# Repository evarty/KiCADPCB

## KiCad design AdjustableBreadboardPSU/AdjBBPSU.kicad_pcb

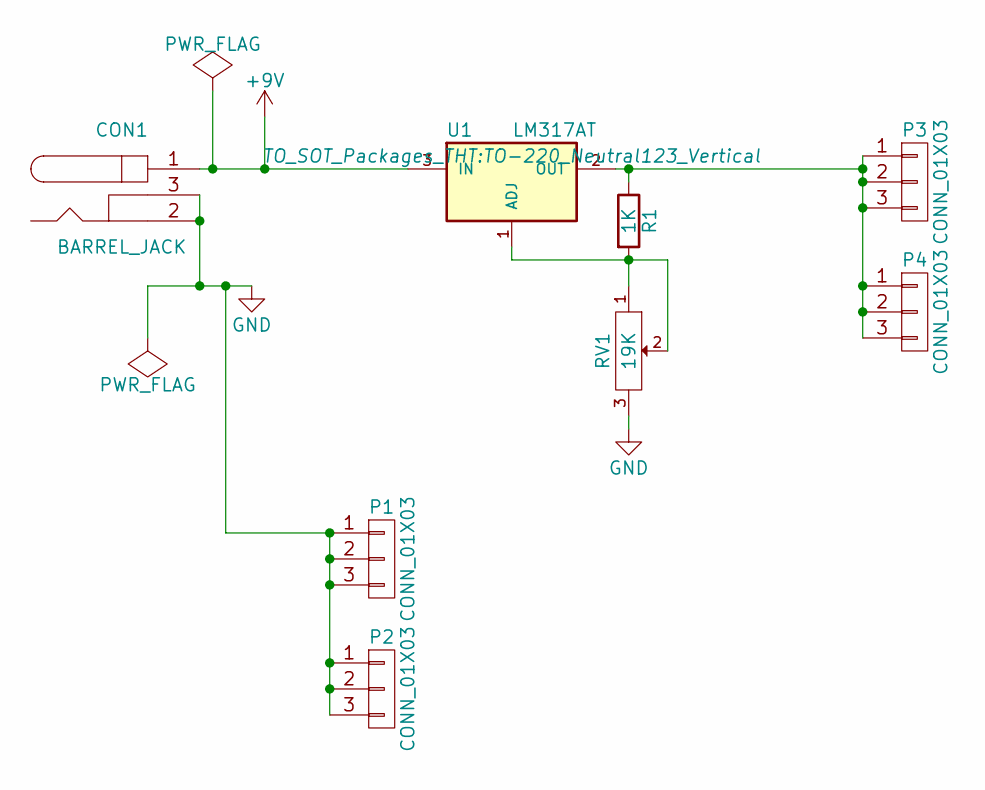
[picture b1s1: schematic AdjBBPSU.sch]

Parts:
CON1: BARREL_JACK
P1, P2, P3, P4: CONN_01X03; Pin_Header_Straight_1x03
R1: 1K; Resistor_Horizontal_RM20mm
RV1: 19K; SalvagedPotFootprint
U1: LM317AT; TO-220_Neutral123_Vertical

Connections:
+9V: CON1.1, U1.3 (IN)
GND: CON1.2, CON1.3, P1.1, P1.2, P1.3, P2.1, P2.2, P2.3, RV1.3
unnamed: P3.1, P3.2, P3.3, P4.1, P4.2, P4.3, R1.1, U1.2 (OUT)
unnamed: R1.2, RV1.1, RV1.2, U1.1 (ADJ)

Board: 2 copper layers, 8 parts (0 on the bottom side), 4 nets, no tracks yet.

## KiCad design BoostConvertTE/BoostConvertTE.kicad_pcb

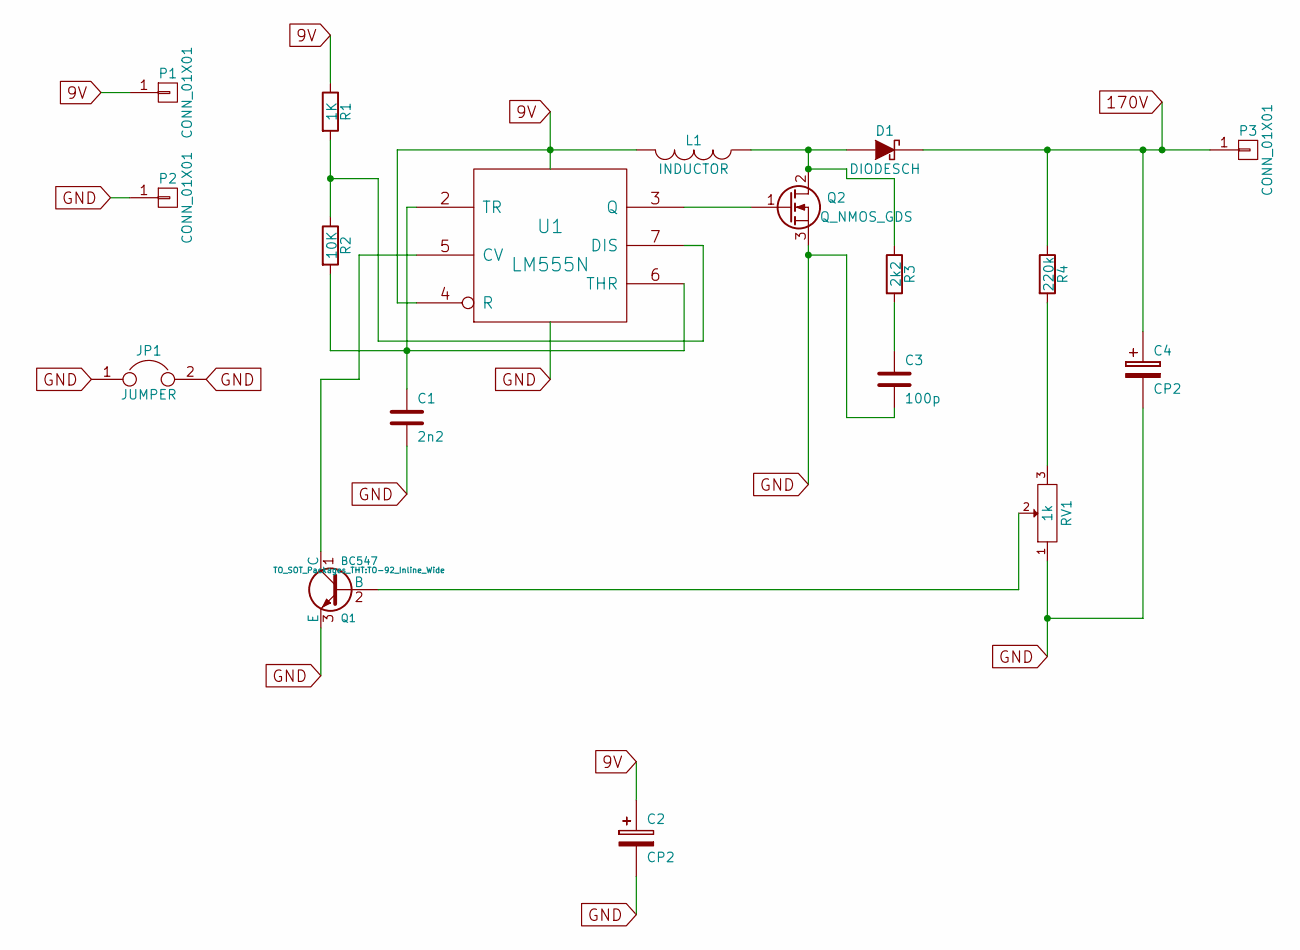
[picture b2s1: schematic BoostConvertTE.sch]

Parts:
C1: 2n2; C_Rect_L7_W2.5_P5
C2: CP2; C_Radial_D10_L13_P5
C3: 100p; C_Rect_L7_W2.5_P5
C4: CP2; C_Rect_L27_W9_H17_P23
D1: DIODESCH; D3
JP1: JUMPER; R3
L1: INDUCTOR; C_Radial_D10_L13_P5
P1, P2, P3: CONN_01X01; Pin_Header_Straight_1x01
Q1: BC547; TO-92_Inline_Wide
Q2: Q_NMOS_GDS; TO-220_Neutral123_Vertical
R1: 1K; Resistor_Horizontal_RM10mm
R2: 10K; Resistor_Horizontal_RM10mm
R3: 2k2; Resistor_Horizontal_RM10mm
R4: 220k; Resistor_Horizontal_RM10mm
RV1: 1k; TO-220_Neutral123_Horizontal
U1: LM555N; DIP-8_W7.62mm_LongPads

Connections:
9V: C2.1, L1.2, P1.1, R1.1, U1.4 (R), U1.8 (VCC)
170V: C4.1, D1.2 (K), P3.1, R4.1
GND: C1.2, C2.2, C3.2, C4.2, JP1.1, JP1.2, P2.1, Q1.3 (E), Q2.3 (S), RV1.1, U1.1 (GND); also elsewhere on the board
unnamed: C1.1, R2.2, U1.2 (TR), U1.6 (THR)
unnamed: C3.1, R3.2
unnamed: D1.1 (A), L1.1, Q2.2 (D), R3.1
unnamed: Q1.1 (C), U1.5 (CV)
unnamed: Q1.2 (B), RV1.2
unnamed: Q2.1 (G), U1.3 (Q)
unnamed: R1.2, R2.1, U1.7 (DIS)
unnamed: R4.2, RV1.3

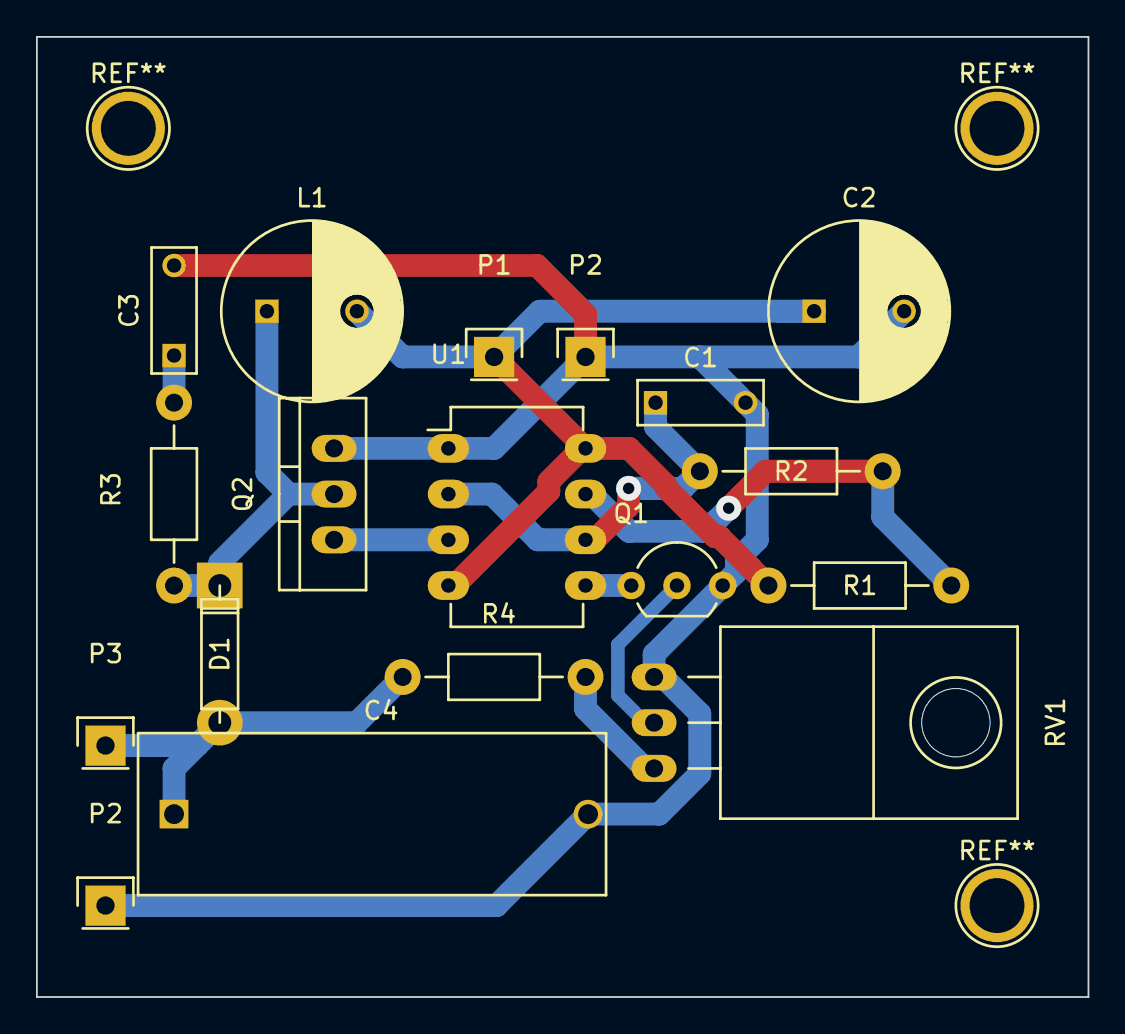
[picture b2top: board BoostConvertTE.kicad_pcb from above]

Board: 2 copper layers, 58.4 x 53.3 mm, 18 parts (0 on the bottom side), 11 nets.

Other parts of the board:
P2#2: CONN_01X01; Pin_Header_Straight_1x01

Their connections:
GND: P2#2.1; also elsewhere on the board

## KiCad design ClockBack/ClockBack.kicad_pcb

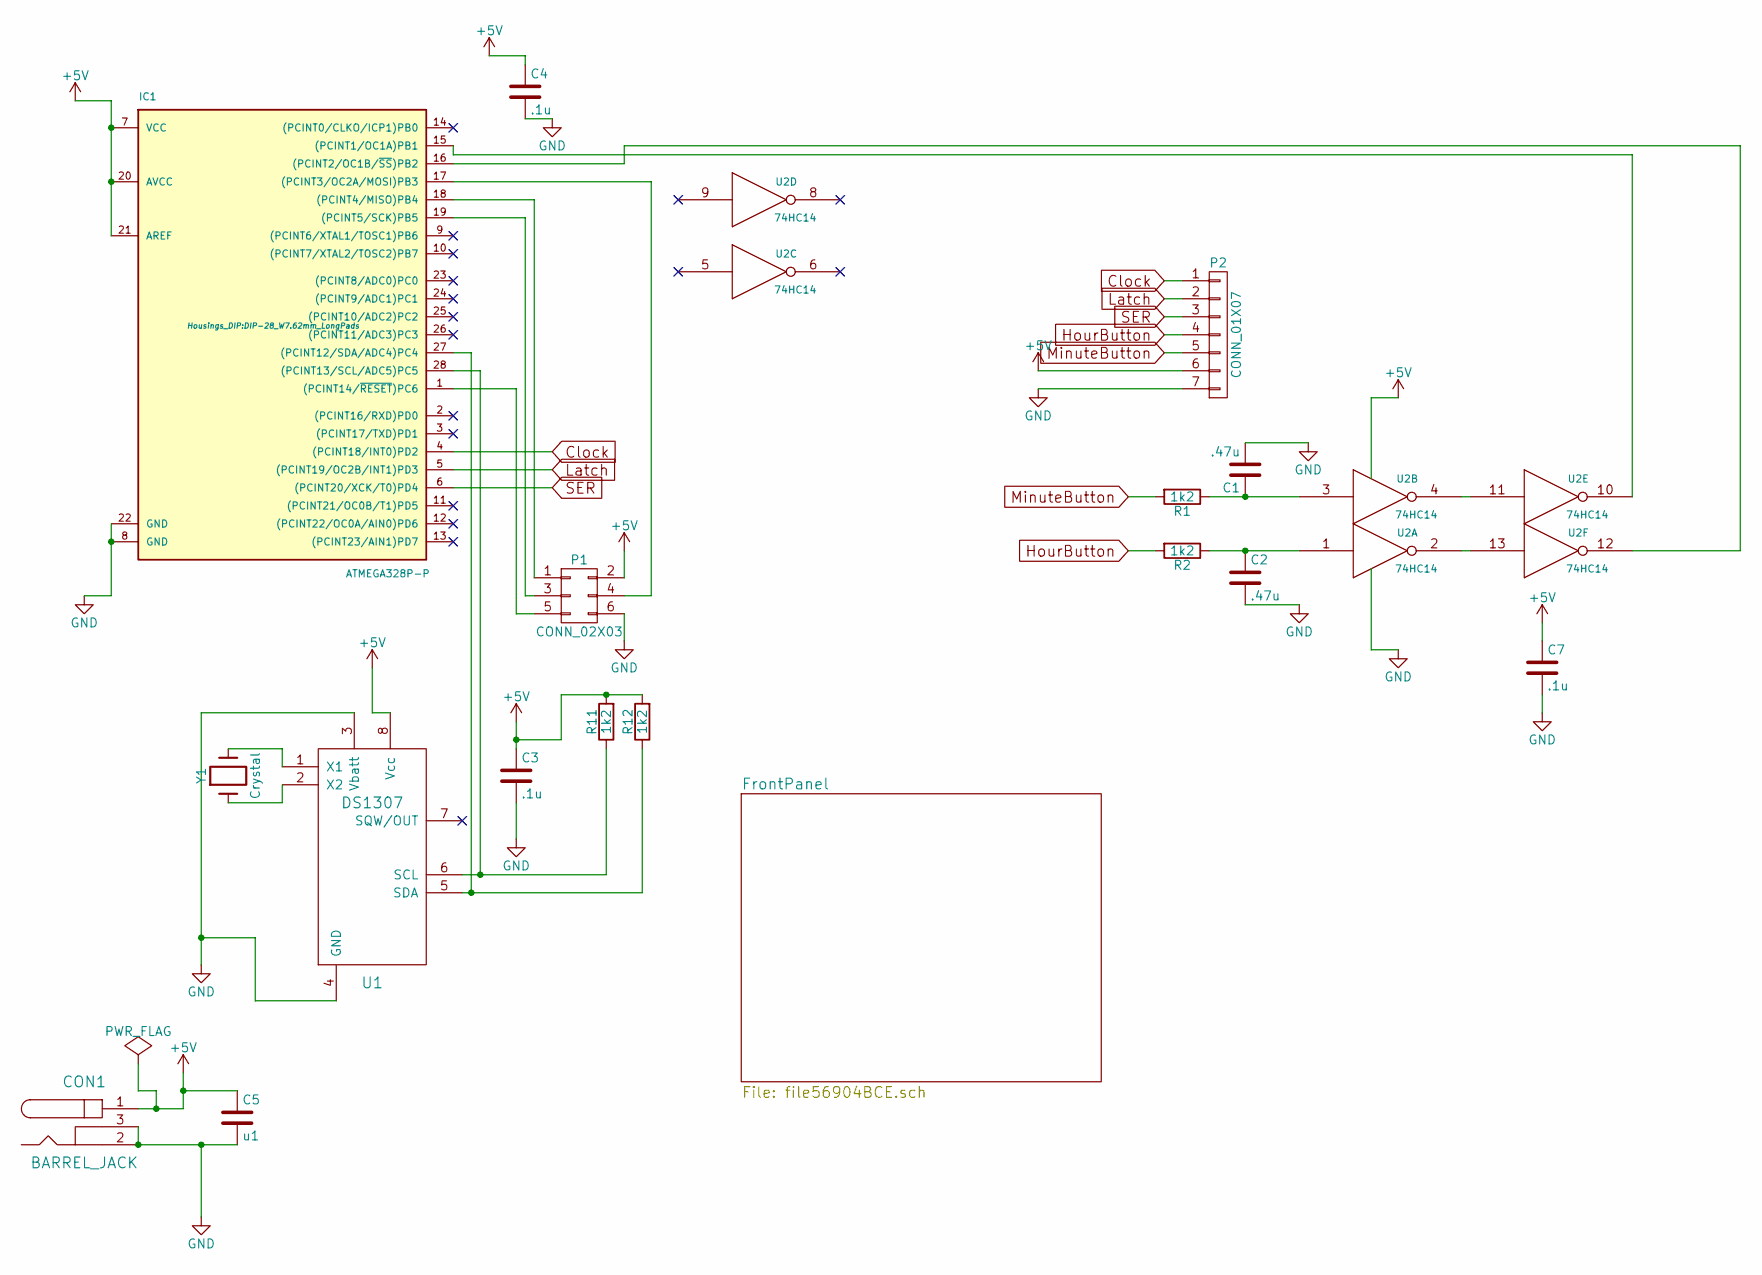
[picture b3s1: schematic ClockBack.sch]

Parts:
C1, C2: .47u; C_Disc_D6_P5
C3, C4, C7: .1u; C_Disc_D6_P5
C5: u1; C_Disc_D6_P5
CON1: BARREL_JACK
IC1: ATMEGA328P-P; DIP-28_W7.62mm_LongPads
P1: CONN_02X03; Pin_Header_Straight_2x03
P2: CONN_01X07; Pin_Header_Straight_1x07
R1, R2, R11, R12: 1k2; Resistor_Horizontal_RM10mm
U1: DS1307; DIP-8_W7.62mm_LongPads
U2: 74HC14; DIP-14_W7.62mm_LongPads
Y1: Crystal; Pin_Header_Straight_1x02

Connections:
Clock: IC1.4 ((PCINT18/INT0)PD2), P2.1; also elsewhere on the board
GND: C1.2, C2.2, C3.2, C4.2, C5.2, C7.2, CON1.2, CON1.3, IC1.8 (GND), IC1.22 (GND), P1.6, P2.7, U1.3 (Vbatt), U1.4 (GND), U2.7 (GND); also elsewhere on the board
Latch: IC1.5 ((PCINT19/OC2B/INT1)PD3), P2.2; also elsewhere on the board
unnamed: C1.1, R1.1, U2.3
unnamed: C2.1, R2.1, U2.1
unnamed: IC1.1 ((PCINT14/~RESET~)PC6), P1.5
unnamed: IC1.15 ((PCINT1/OC1A)PB1), U2.10
unnamed: IC1.16 ((PCINT2/OC1B/~SS~)PB2), U2.12
unnamed: IC1.17 ((PCINT3/OC2A/MOSI)PB3), P1.4
unnamed: IC1.18 ((PCINT4/MISO)PB4), P1.1
unnamed: IC1.19 ((PCINT5/SCK)PB5), P1.3
unnamed: IC1.27 ((PCINT12/SDA/ADC4)PC4), R12.1, U1.5 (SDA)
unnamed: IC1.28 ((PCINT13/SCL/ADC5)PC5), R11.1, U1.6 (SCL)
unnamed: U1.1 (X1), Y1.2
unnamed: U1.2 (X2), Y1.1
unnamed: U2.4, U2.11
unnamed: U2.2, U2.13
SER: IC1.6 ((PCINT20/XCK/T0)PD4), P2.3; also elsewhere on the board

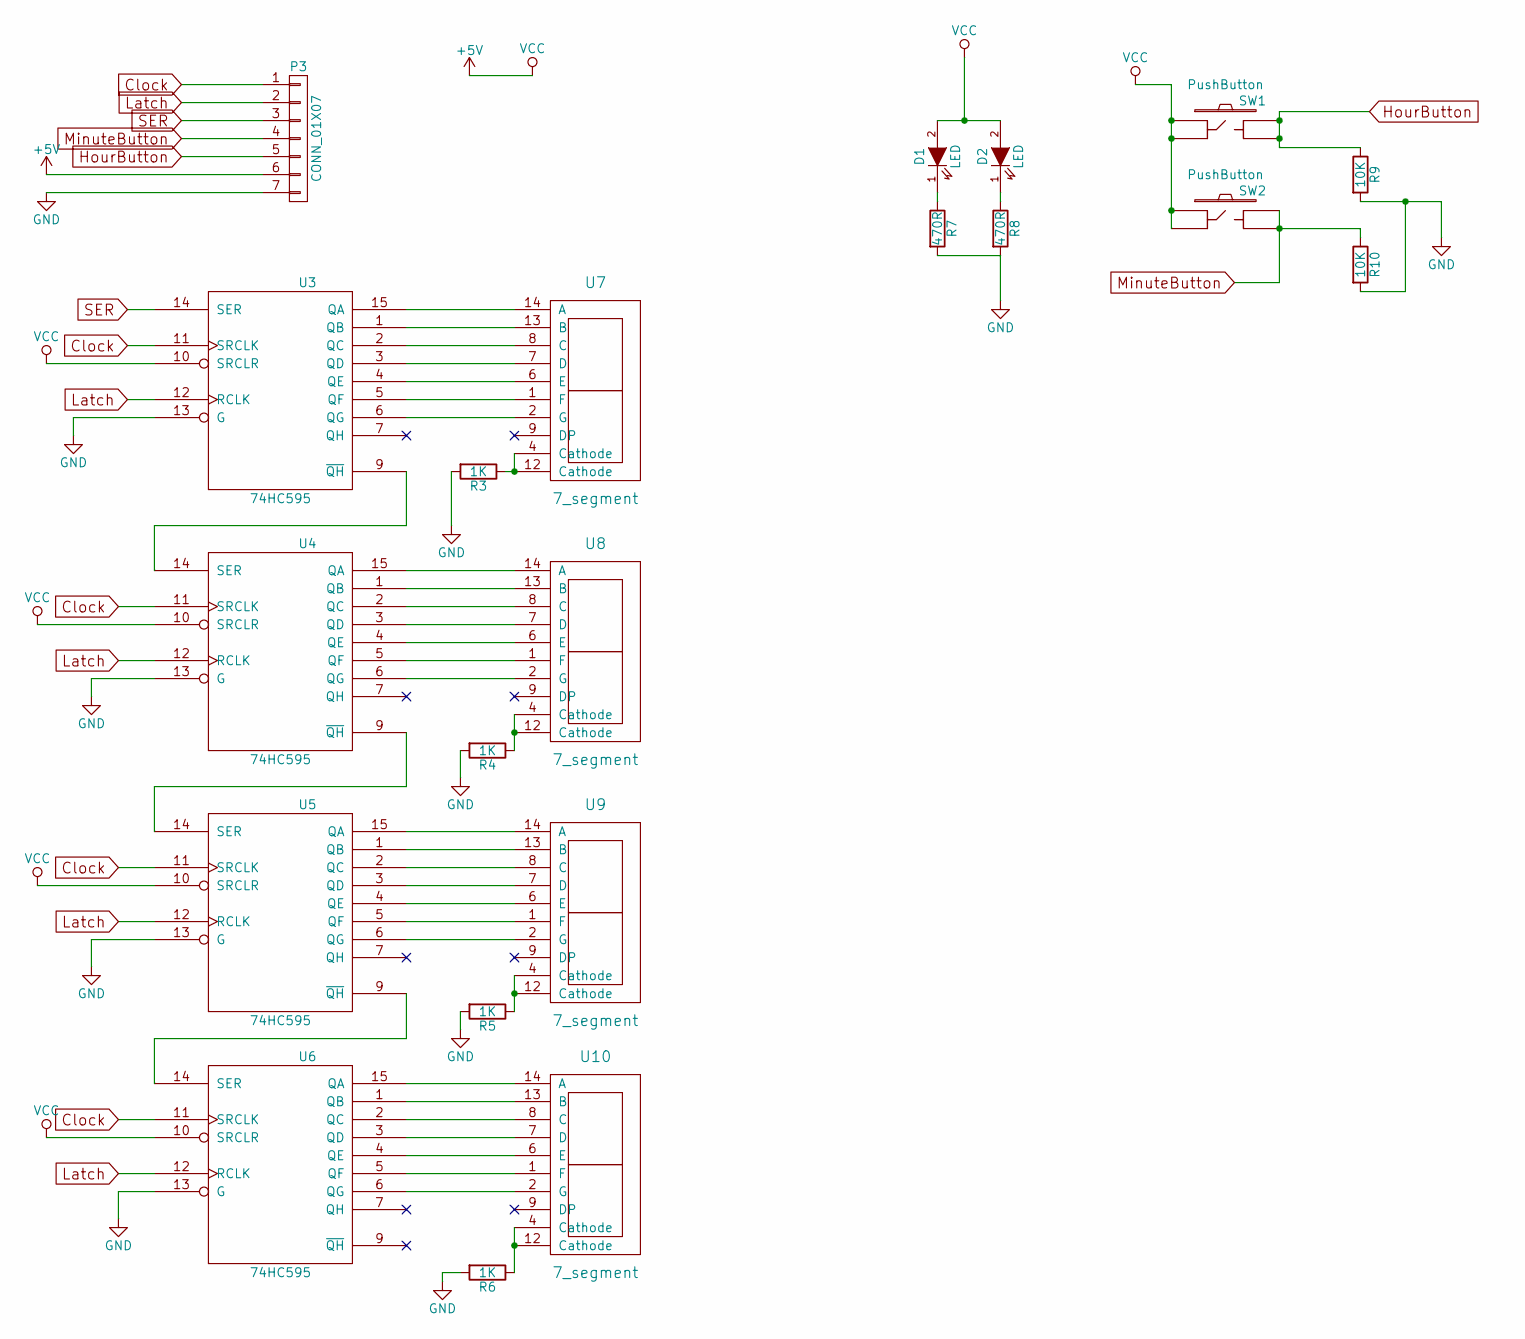
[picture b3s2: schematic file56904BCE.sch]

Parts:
D1, D2: LED; LED-5MM
P3: CONN_01X07; Socket_Strip_Straight_1x07
R3, R4, R5, R6: 1K; Resistor_Horizontal_RM10mm
R7, R8: 470R; Resistor_Horizontal_RM10mm
R9, R10: 10K; Resistor_Horizontal_RM10mm
SW1, SW2: PushButton
U3, U4, U5, U6: 74HC595; DIP-16_W7.62mm_LongPads
U7, U8, U9, U10: 7_segment; MAN3640A

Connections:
Clock: P3.1, U3.11 (SRCLK), U4.11 (SRCLK), U5.11 (SRCLK), U6.11 (SRCLK); also elsewhere on the board
GND: P3.7, R3.2, R4.2, R5.2, R6.2, R7.2, R8.2, R9.2, R10.2, U3.8 (GND), U3.13 (G), U4.8 (GND), U4.13 (G), U5.8 (GND), U5.13 (G), U6.8 (GND), U6.13 (G); also elsewhere on the board
Latch: P3.2, U3.12 (RCLK), U4.12 (RCLK), U5.12 (RCLK), U6.12 (RCLK); also elsewhere on the board
unnamed: D1.1 (K), R7.1
unnamed: D2.1 (K), R8.1
unnamed: R3.1, U7.4 (Cathode), U7.12 (Cathode)
unnamed: R4.1, U8.4 (Cathode), U8.12 (Cathode)
unnamed: R5.1, U9.4 (Cathode), U9.12 (Cathode)
unnamed: R6.1, U10.4 (Cathode), U10.12 (Cathode)
unnamed: U3.1 (QB), U7.13 (B)
unnamed: U3.2 (QC), U7.8 (C)
unnamed: U3.3 (QD), U7.7 (D)
unnamed: U3.4 (QE), U7.6 (E)
unnamed: U3.5 (QF), U7.1 (F)
unnamed: U3.6 (QG), U7.2 (G)
unnamed: U3.9 (~QH), U4.14 (SER)
unnamed: U3.15 (QA), U7.14 (A)
unnamed: U4.1 (QB), U8.13 (B)
unnamed: U4.2 (QC), U8.8 (C)
unnamed: U4.3 (QD), U8.7 (D)
unnamed: U4.4 (QE), U8.6 (E)
unnamed: U4.5 (QF), U8.1 (F)
unnamed: U4.6 (QG), U8.2 (G)
unnamed: U4.9 (~QH), U5.14 (SER)
unnamed: U4.15 (QA), U8.14 (A)
unnamed: U5.1 (QB), U9.13 (B)
unnamed: U5.2 (QC), U9.8 (C)
unnamed: U5.3 (QD), U9.7 (D)
unnamed: U5.4 (QE), U9.6 (E)
unnamed: U5.5 (QF), U9.1 (F)
unnamed: U5.6 (QG), U9.2 (G)
unnamed: U5.9 (~QH), U6.14 (SER)
unnamed: U5.15 (QA), U9.14 (A)
unnamed: U6.5 (QF), U10.1 (F)
unnamed: U6.6 (QG), U10.2 (G)
unnamed: U6.4 (QE), U10.6 (E)
unnamed: U6.3 (QD), U10.7 (D)
unnamed: U6.2 (QC), U10.8 (C)
unnamed: U6.1 (QB), U10.13 (B)
unnamed: U6.15 (QA), U10.14 (A)
SER: P3.3, U3.14 (SER); also elsewhere on the board

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
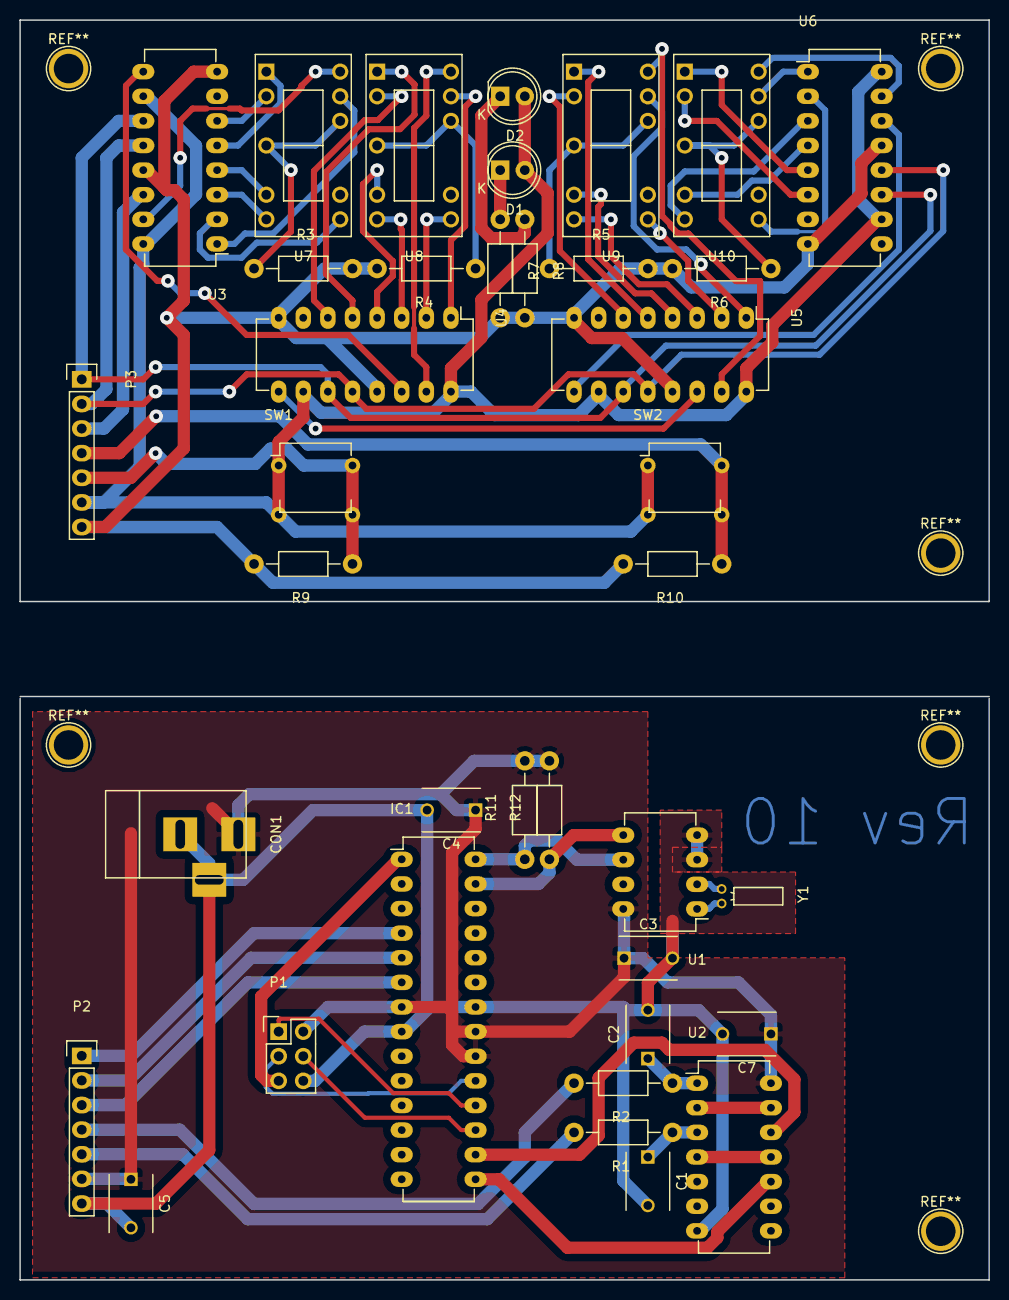
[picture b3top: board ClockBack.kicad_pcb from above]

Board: 2 copper layers, 100.0 x 130.0 mm, 38 parts (0 on the bottom side), 58 nets.

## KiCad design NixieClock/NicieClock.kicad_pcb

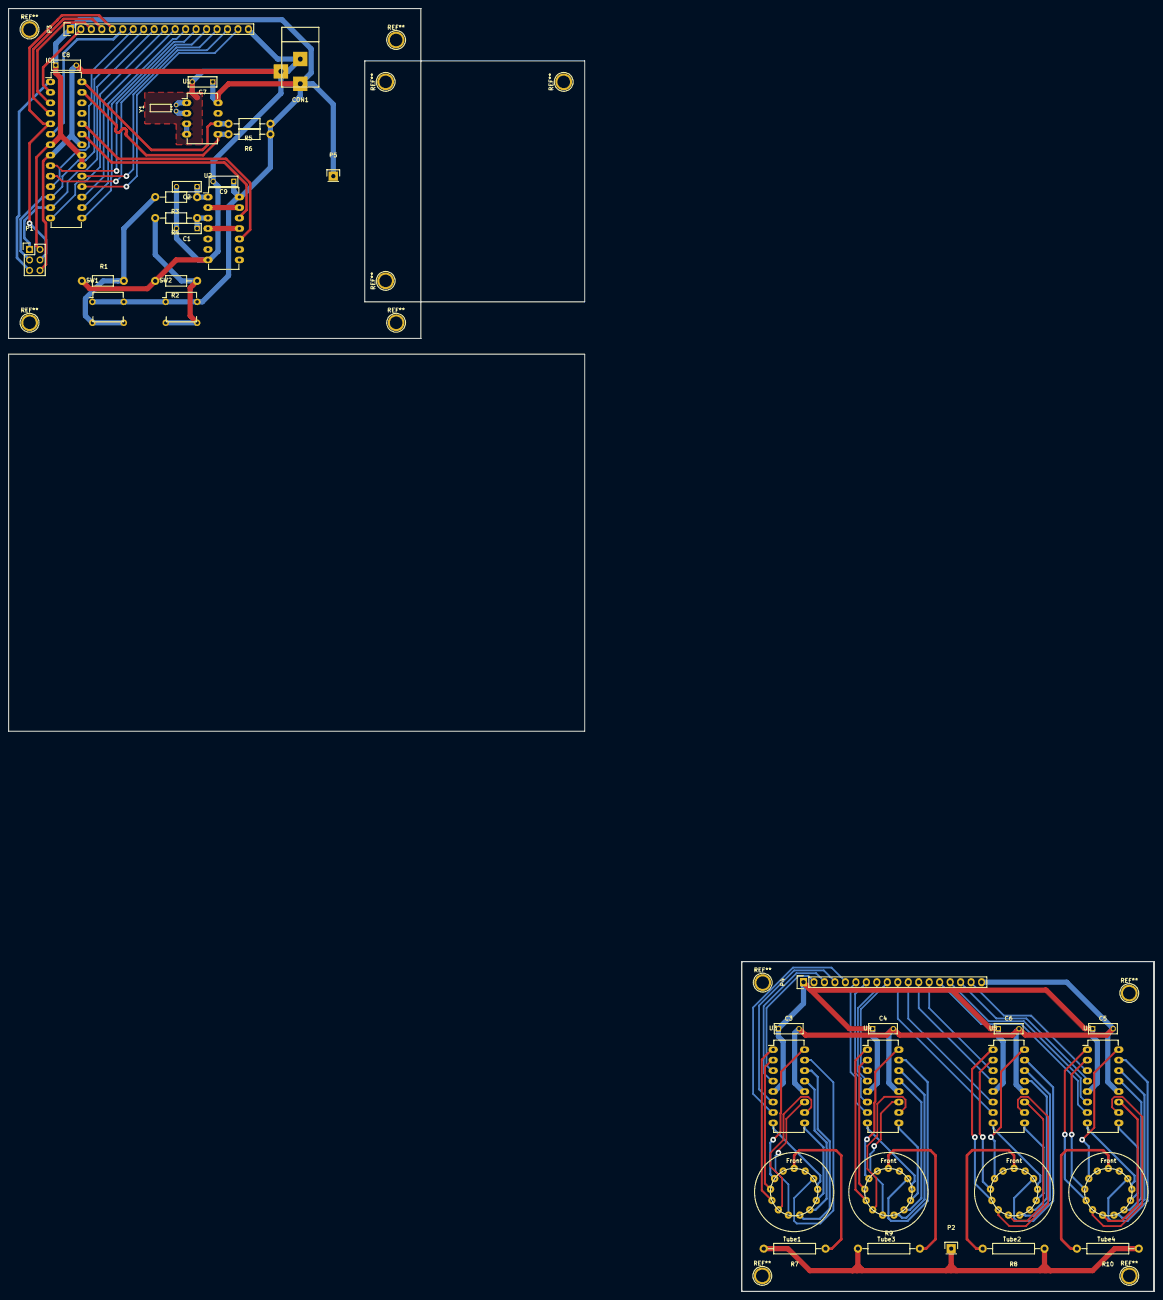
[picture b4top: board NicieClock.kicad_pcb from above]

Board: 2 copper layers, 277.8 x 311.1 mm, 39 parts (0 on the bottom side), 76 nets.

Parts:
C1, C2: .47u; C_Rect_L7_W2.5_P5
C3, C4, C5, C6, C7, C8, C9: .1u; C_Rect_L7_W2.5_P5
CON1: BARREL_JACK
IC1: ATMEGA328P-P; DIP-28_W7.62mm_LongPads
P1: CONN_02X03; Pin_Header_Straight_2x03
P2, P5: CONN_01X01; Pin_Header_Straight_1x01
P3, P4: CONN_01X18; Pin_Header_Straight_1x18
R1, R2: 10K; Resistor_Horizontal_RM10mm
R3, R4: 1K2; Resistor_Horizontal_RM10mm
R5, R6: 10k; Resistor_Horizontal_RM10mm
R7, R8, R9, R10: 47K; Resistor_Horizontal_RM15mm
SW1, SW2: PushButton
Tube1, Tube2, Tube3, Tube4: IN-14
U1: DS1307; DIP-8_W7.62mm_LongPads
U2: 74HC14; DIP-14_W7.62mm_LongPads
U3, U4, U5, U6: 74141; DIP-16_W7.62mm_LongPads
Y1: Crystal; Crystal_Round_Horizontal_2mm

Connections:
170V: P2.1, R7.2, R8.1, R9.1, R10.1
+5V: C3.1, C4.1, C5.1, C6.1, C7.1, C8.1, C9.1, CON1.1, IC1.7, IC1.20, IC1.21, P1.2, P3.1, P4.1, P5.1, R5.1, R6.1, SW1.1, SW1.4, SW2.1, SW2.4, U1.8, U2.14, U3.5, U4.5, U5.5, U6.5
GND: C1.2, C2.2, C3.2, C4.2, C5.2, C6.2, C7.2, C8.2, C9.2, CON1.2, CON1.3, IC1.8, IC1.22, P1.6, P3.18, P4.18, R1.1, R2.2, U1.3, U1.4, U2.7, U3.12, U4.12, U5.12, U6.12
HourButton: IC1.24, U2.10
HourOnesA: IC1.13, P1.1, P3.9, P4.9, U4.3
HourOnesB: IC1.11, P3.7, P4.7, U4.6
HourOnesC: IC1.6, P3.6, P4.6, U4.7
HourOnesD: IC1.12, P1.3, P3.8, P4.8, U4.4
HourTensA: IC1.2, P3.2, P4.2, U3.3
HourTensB: IC1.4, P3.4, P4.4, U3.6
HourTensC: IC1.5, P1.4, P3.5, P4.5, U3.7
HourTensD: IC1.3, P3.3, P4.3, U3.4
MinButton: IC1.23, U2.12
MinOnesA: IC1.18, P3.17, P4.17, U6.3
MinOnesB: IC1.10, P3.15, P4.15, U6.6
MinOnesC: IC1.9, P3.14, P4.14, U6.7
MinOnesD: IC1.19, P3.16, P4.16, U6.4
MinTensA: IC1.15, P3.13, P4.13, U5.3
MinTensB: IC1.17, P3.11, P4.11, U5.6
MinTensC: IC1.14, P3.10, P4.10, U5.7
MinTensD: IC1.16, P3.12, P4.12, U5.4
unnamed: C1.1, R4.1, U2.3
unnamed: C2.1, R3.1, U2.1
unnamed: R1.2, R3.2, SW1.2, SW1.3
unnamed: R2.1, R4.2, SW2.2, SW2.3
unnamed: R7.1, Tube1.1
unnamed: R8.2, Tube2.1
unnamed: R9.2, Tube3.1
unnamed: R10.2, Tube4.1
unnamed: Tube1.3, U3.15
unnamed: Tube1.4, U3.8
unnamed: Tube1.5, U3.9
unnamed: Tube1.6, U3.13
unnamed: Tube1.7, U3.14
unnamed: Tube1.8, U3.11
unnamed: Tube1.9, U3.10
unnamed: Tube1.10, U3.1
unnamed: Tube1.11, U3.2
unnamed: Tube1.12, U3.16
unnamed: Tube2.3, U5.15
unnamed: Tube2.4, U5.8
unnamed: Tube2.5, U5.9
unnamed: Tube2.6, U5.13
unnamed: Tube2.7, U5.14
unnamed: Tube2.8, U5.11
unnamed: Tube2.9, U5.10
unnamed: Tube2.10, U5.1
unnamed: Tube2.11, U5.2
unnamed: Tube2.12, U5.16
unnamed: Tube3.3, U4.15
unnamed: Tube3.4, U4.8
unnamed: Tube3.5, U4.9
unnamed: Tube3.6, U4.13
unnamed: Tube3.7, U4.14
unnamed: Tube3.8, U4.11
unnamed: Tube3.9, U4.10
unnamed: Tube3.10, U4.1
unnamed: Tube3.11, U4.2
unnamed: Tube3.12, U4.16
unnamed: Tube4.3, U6.15
unnamed: Tube4.4, U6.8
unnamed: Tube4.5, U6.9
unnamed: Tube4.6, U6.13
unnamed: Tube4.7, U6.14
unnamed: Tube4.8, U6.11
unnamed: Tube4.9, U6.10
unnamed: Tube4.10, U6.1
unnamed: Tube4.11, U6.2
unnamed: Tube4.12, U6.16
unnamed: U1.1, Y1.2
unnamed: U1.2, Y1.1
unnamed: U2.4, U2.11
unnamed: U2.2, U2.13
RESET: IC1.1, P1.5
SCL: IC1.28, R5.2, U1.6
SDA: IC1.27, R6.2, U1.5
